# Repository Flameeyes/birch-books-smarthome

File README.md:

<!--
SPDX-FileCopyrightText: 2020 The birch-books-smarthome Authors

SPDX-License-Identifier: MIT
-->

# Birch Books Smart Home

This repository contains code, schematics, documentation and notes to implement a
MCU-controlled LED lights system for the [LEGO Creator Bookshop
set](https://www.lego.com/en-gb/product/bookshop-10270) (10270).

## Further References

Refer to my [blog posts](https://flameeyes.blog/tag/birch-books/) for details.

You can see some pictures of the results on [my Flickr
album](https://www.flickr.com/photos/flameeyes/albums/72157714292772872).

## License

Copyright 2020 The birch-books-smarthome authors.

Permission is hereby granted, free of charge, to any person obtaining a copy of this
software and associated documentation files (the "Software"), to deal in the Software
without restriction, including without limitation the rights to use, copy, modify,
merge, publish, distribute, sublicense, and/or sell copies of the Software, and to
permit persons to whom the Software is furnished to do so, subject to the following
conditions:

The above copyright notice and this permission notice shall be included in all copies or
substantial portions of the Software.

THE SOFTWARE IS PROVIDED "AS IS", WITHOUT WARRANTY OF ANY KIND, EXPRESS OR IMPLIED,
INCLUDING BUT NOT LIMITED TO THE WARRANTIES OF MERCHANTABILITY, FITNESS FOR A PARTICULAR
PURPOSE AND NONINFRINGEMENT. IN NO EVENT SHALL THE AUTHORS OR COPYRIGHT HOLDERS BE
LIABLE FOR ANY CLAIM, DAMAGES OR OTHER LIABILITY, WHETHER IN AN ACTION OF CONTRACT, TORT
OR OTHERWISE, ARISING FROM, OUT OF OR IN CONNECTION WITH THE SOFTWARE OR THE USE OR
OTHER DEALINGS IN THE SOFTWARE.

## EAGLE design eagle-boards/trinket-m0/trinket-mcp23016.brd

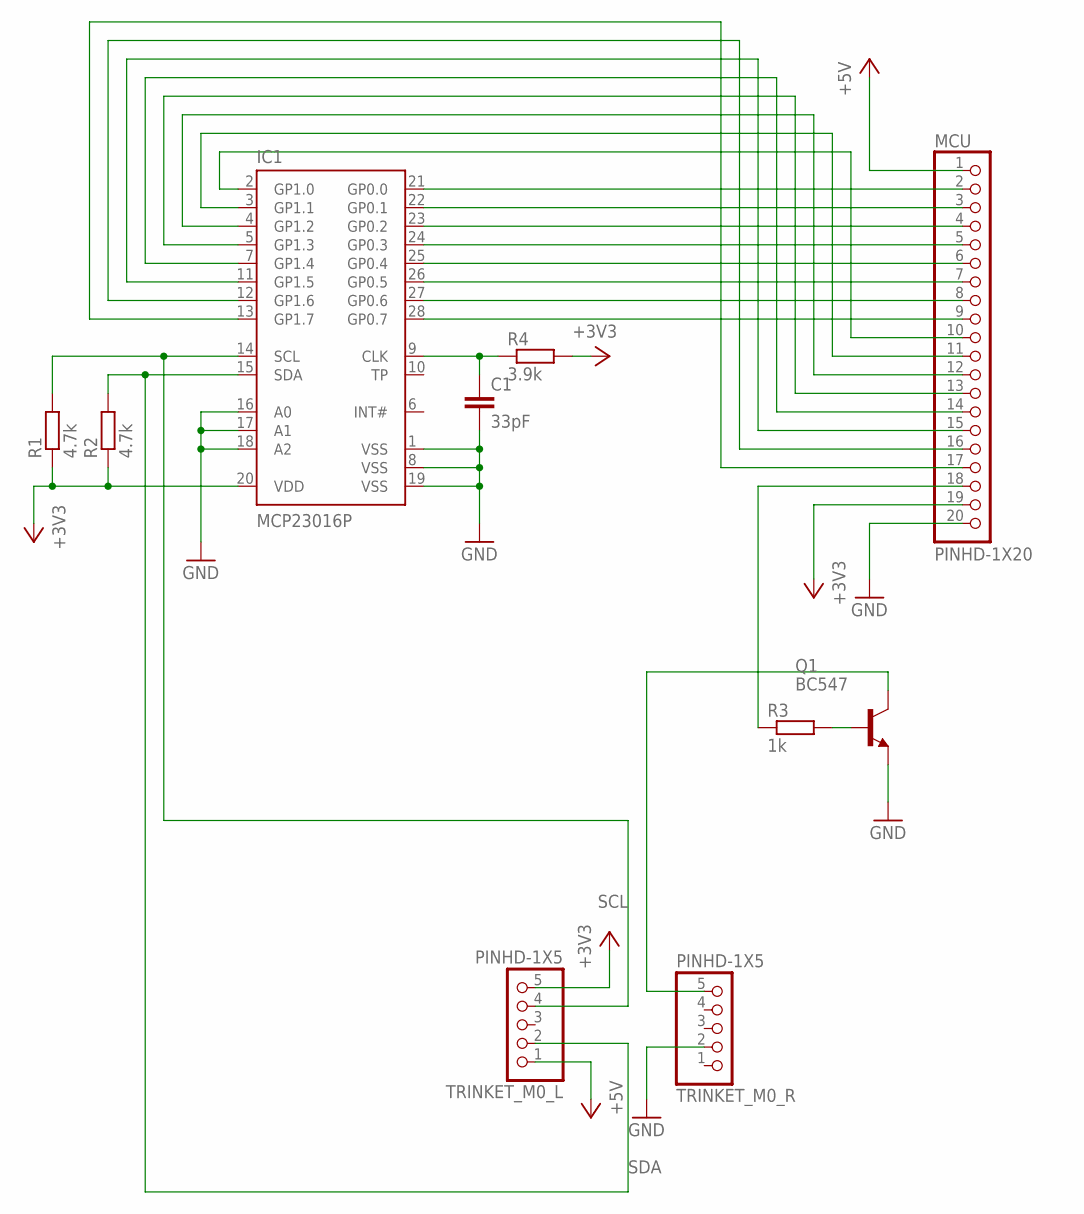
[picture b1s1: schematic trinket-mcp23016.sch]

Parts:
C1: 33pF; C025-025X050
IC1: MCP23016P; DIL28-3
MCU: PINHD-1X20; 1X20
Q1: BC547; TO92
R1, R2: 4.7k; 0207/10
R3: 1k; 0207/10
R4: 3.9k; 0207/10
TRINKET_M0_L, TRINKET_M0_R: PINHD-1X5; 1X05

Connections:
+3V3: IC1.20 (VDD), MCU.19, R1.1, R2.1, R4.2, TRINKET_M0_L.5
+5V: MCU.1, TRINKET_M0_L.1
GND: C1.2, IC1.1 (VSS), IC1.8 (VSS), IC1.16 (A0), IC1.17 (A1), IC1.18 (A2), IC1.19 (VSS), MCU.20, Q1.1 (E), TRINKET_M0_R.2
unnamed: IC1.21 (GP0.0), MCU.2
unnamed: IC1.22 (GP0.1), MCU.3
unnamed: IC1.23 (GP0.2), MCU.4
unnamed: IC1.24 (GP0.3), MCU.5
unnamed: IC1.25 (GP0.4), MCU.6
unnamed: IC1.26 (GP0.5), MCU.7
unnamed: IC1.27 (GP0.6), MCU.8
unnamed: IC1.28 (GP0.7), MCU.9
unnamed: IC1.2 (GP1.0), MCU.10
unnamed: IC1.3 (GP1.1), MCU.11
unnamed: IC1.4 (GP1.2), MCU.12
unnamed: IC1.5 (GP1.3), MCU.13
unnamed: IC1.7 (GP1.4), MCU.14
unnamed: IC1.11 (GP1.5), MCU.15
unnamed: IC1.12 (GP1.6), MCU.16
unnamed: IC1.13 (GP1.7), MCU.17
unnamed: Q1.2 (B), R3.2
unnamed: MCU.18, R3.1
unnamed: Q1.3 (C), TRINKET_M0_R.5
unnamed: C1.1, IC1.9 (CLK), R4.1
SCL: IC1.14 (SCL), R1.2, TRINKET_M0_L.4
SDA: IC1.15 (SDA), R2.2, TRINKET_M0_L.2

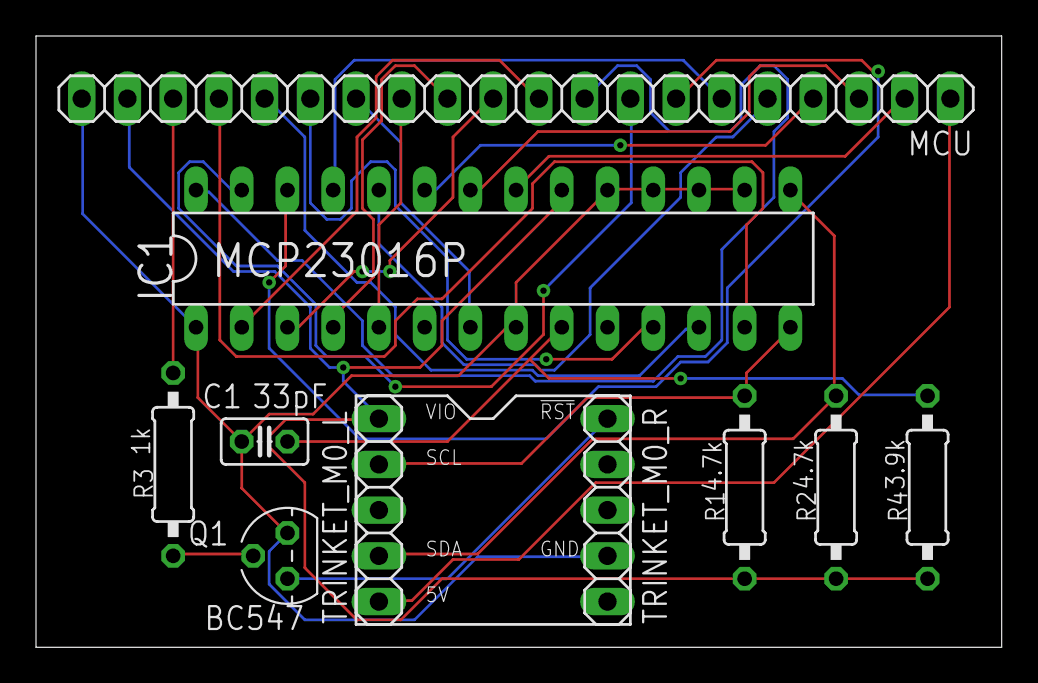
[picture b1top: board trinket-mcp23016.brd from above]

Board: 2 copper layers, 53.6 x 34.0 mm, 10 parts (0 on the bottom side), 25 nets.

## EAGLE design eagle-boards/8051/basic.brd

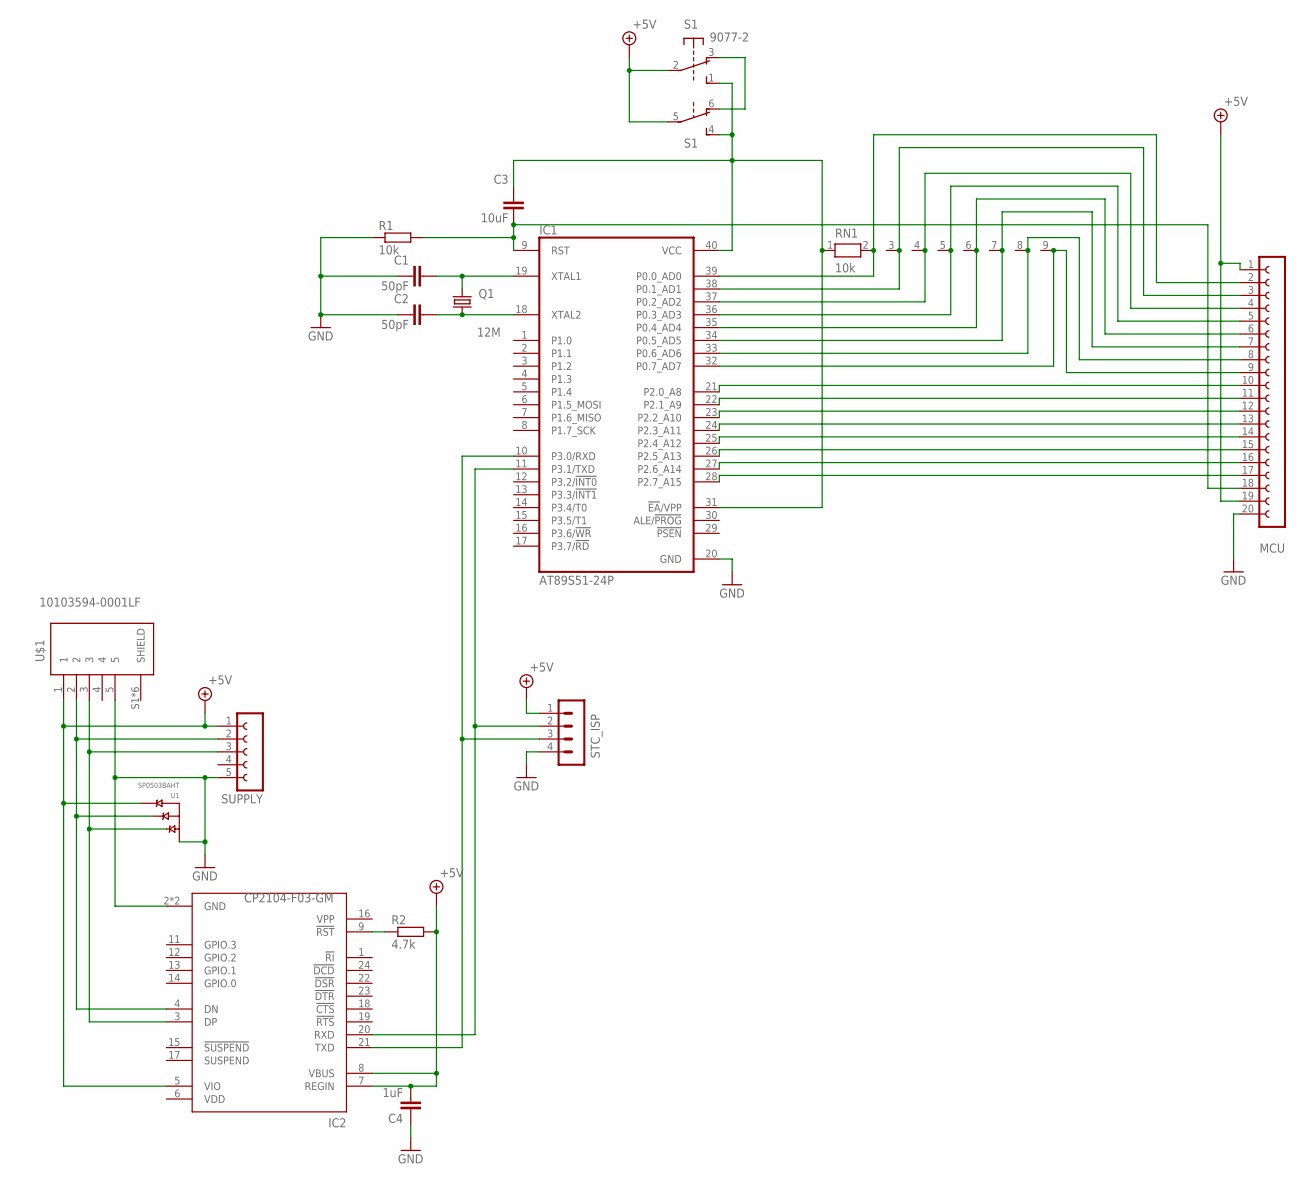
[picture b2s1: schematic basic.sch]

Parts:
C1, C2: 50pF; C050-025X075
C3: 10uF; C025-025X050
C4: 1uF; C025-025X050
IC1: AT89S51-24P; DIL40
IC2: CP2104-F03-GM; QFN50P400X400X80-25N
MCU: FE20-1; FE20
Q1: 12M; HC49U70
R1: 10k; 0207/10
R2: 4.7k; 0207/10
RN1: 10k; RN-9
S1: 9077-2
STC_ISP: MA04-1
SUPPLY: FE05-1
U1: SP0503BAHT; SOT143
U$1: 10103594-0001LF; FCI_10103594-0001LF

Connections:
+5V: C4.2, IC2.5 (VIO), IC2.7 (REGIN), IC2.8 (VBUS), MCU.1, MCU.19, R2.2, S1.2, S1.5, STC_ISP.1, SUPPLY.1, U1.4 (C), U$1.1
GND: C1.1, C2.1, C4.1, IC1.20 (GND), IC2.2 (GND), IC2.25 (GND), MCU.20, R1.1, STC_ISP.4, SUPPLY.5, U1.1 (GND), U$1.5
unnamed: IC2.4 (DN), SUPPLY.2, U1.3 (B), U$1.2
unnamed: IC1.28 (P2.7_A15), MCU.17
unnamed: C1.2, IC1.19 (XTAL1), Q1.2
unnamed: C2.2, IC1.18 (XTAL2), Q1.1
unnamed: C3.2, IC1.9 (RST), MCU.18, R1.2
unnamed: IC1.27 (P2.6_A14), MCU.16
unnamed: IC1.38 (P0.1_AD1), MCU.3, RN1.3
unnamed: IC1.26 (P2.5_A13), MCU.15
unnamed: IC1.25 (P2.4_A12), MCU.14
unnamed: IC1.36 (P0.3_AD3), MCU.5, RN1.5
unnamed: IC1.35 (P0.4_AD4), MCU.6, RN1.6
unnamed: IC1.34 (P0.5_AD5), MCU.7, RN1.7
unnamed: IC1.33 (P0.6_AD6), MCU.8, RN1.8
unnamed: IC1.32 (P0.7_AD7), MCU.9, RN1.9
unnamed: IC1.24 (P2.3_A11), MCU.13
unnamed: IC1.23 (P2.2_A10), MCU.12
unnamed: IC1.22 (P2.1_A9), MCU.11
unnamed: IC1.10 (P3.0/RXD), IC2.21 (TXD), STC_ISP.3
unnamed: IC1.21 (P2.0_A8), MCU.10
unnamed: IC2.3 (DP), SUPPLY.3, U1.2 (A), U$1.3
unnamed: IC1.37 (P0.2_AD2), MCU.4, RN1.4
unnamed: S1.3 (O), S1.6 (O)
unnamed: IC2.9 (!RST!), R2.1
unnamed: IC1.39 (P0.0_AD0), MCU.2, RN1.2
unnamed: C3.1, IC1.31 (!EA!/VPP), IC1.40 (VCC), RN1.1, S1.1 (S), S1.4 (S)
unnamed: IC1.11 (P3.1/TXD), IC2.20 (RXD), STC_ISP.2
VDD: IC2.6 (VDD)

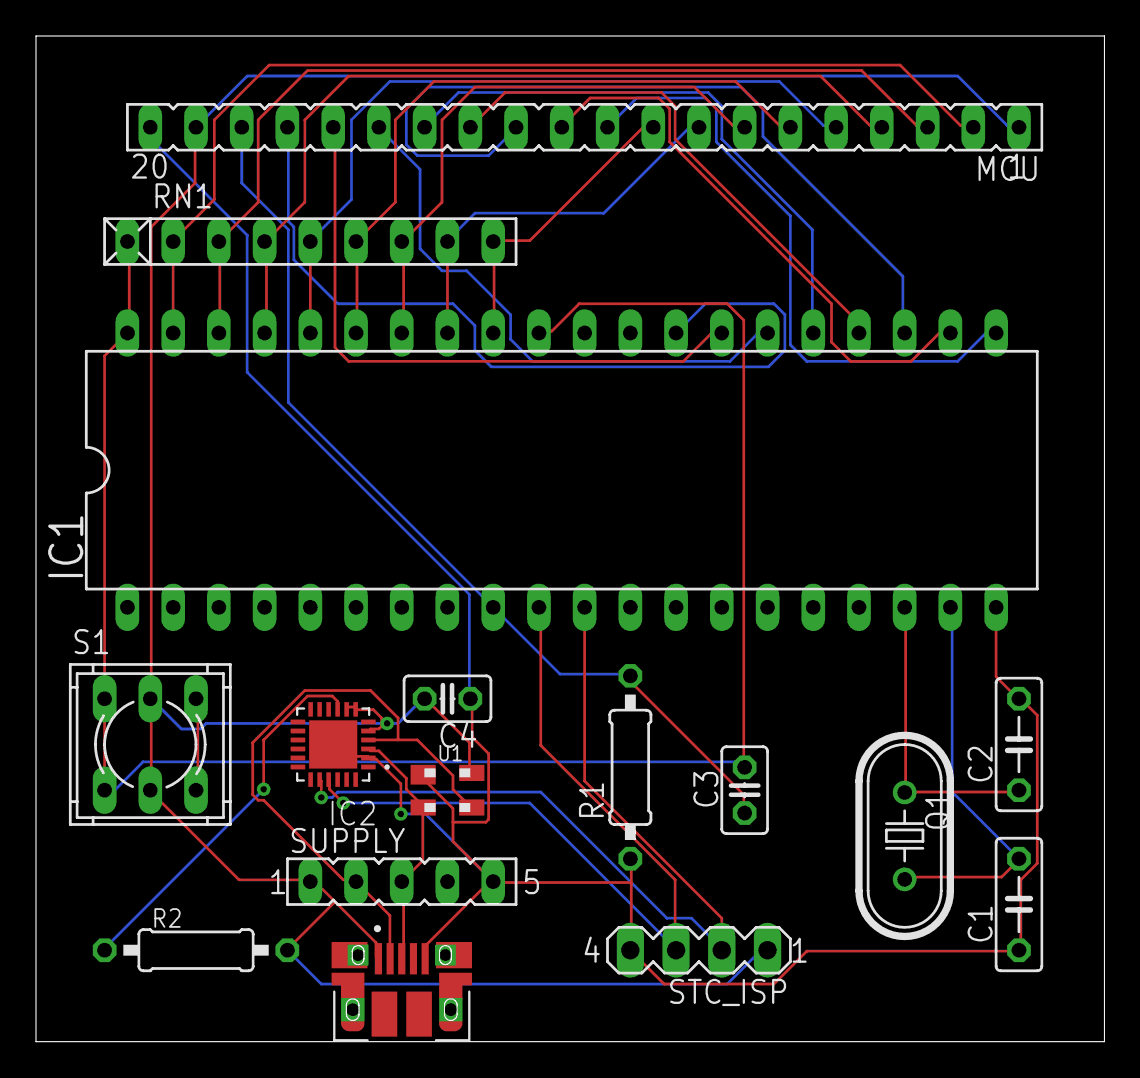
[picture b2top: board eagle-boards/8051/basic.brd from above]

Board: 2 copper layers, 59.4 x 55.9 mm, 16 parts (0 on the bottom side), 28 nets.

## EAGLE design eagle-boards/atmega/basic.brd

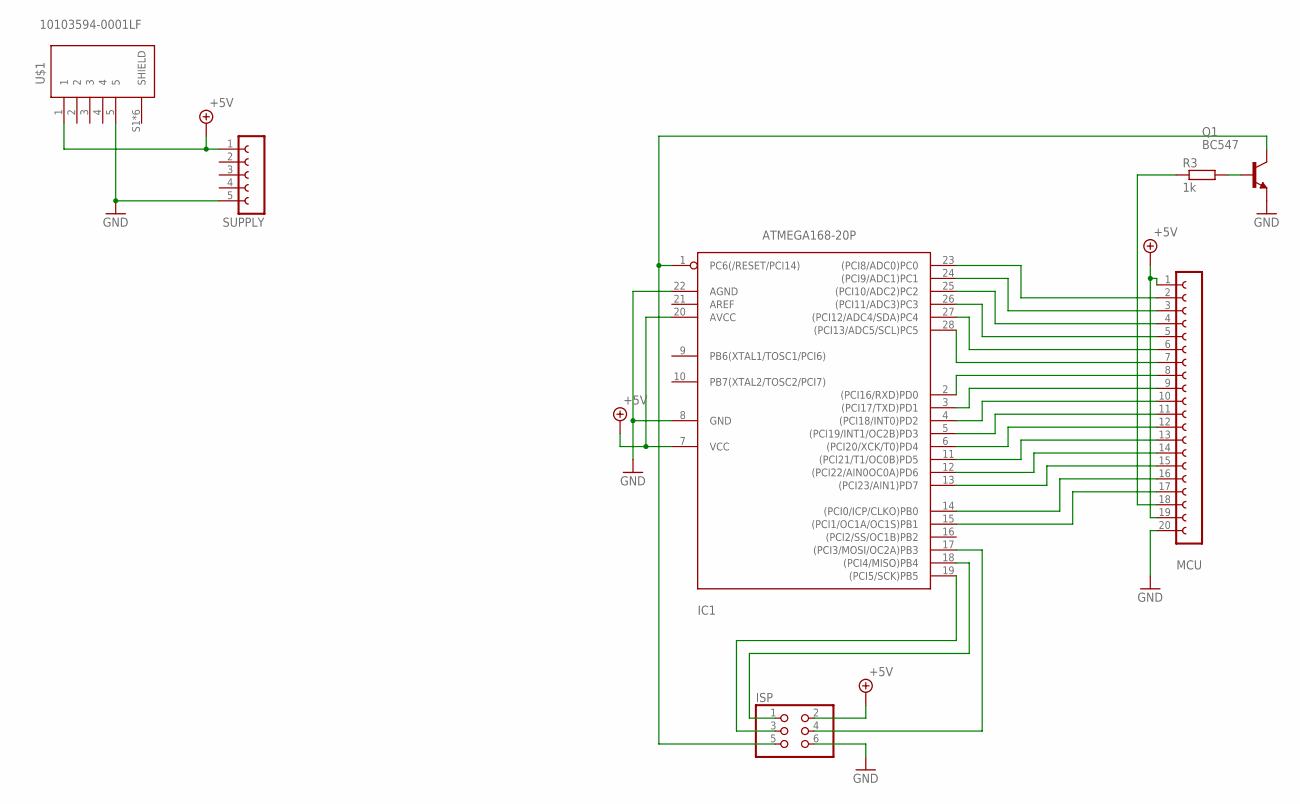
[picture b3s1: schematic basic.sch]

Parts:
IC1: ATMEGA168-20P; DIL28-3
ISP: PINHD-2X3; 2X03
MCU: FE20-1; FE20
Q1: BC547; TO92
R3: 1k; 0207/10
SUPPLY: FE05-1
U$1: 10103594-0001LF; FCI_10103594-0001LF

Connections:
+5V: IC1.7 (VCC), IC1.20 (AVCC), ISP.2, MCU.1, MCU.19, SUPPLY.1, U$1.1
GND: IC1.8 (GND), IC1.22 (AGND), ISP.6, MCU.20, Q1.1 (E), SUPPLY.5, U$1.5
unnamed: IC1.17 ((PCI3/MOSI/OC2A)PB3), ISP.4
unnamed: MCU.18, R3.1
unnamed: IC1.18 ((PCI4/MISO)PB4), ISP.1
unnamed: IC1.19 ((PCI5/SCK)PB5), ISP.3
unnamed: IC1.23 ((PCI8/ADC0)PC0), MCU.2
unnamed: IC1.24 ((PCI9/ADC1)PC1), MCU.3
unnamed: IC1.25 ((PCI10/ADC2)PC2), MCU.4
unnamed: IC1.26 ((PCI11/ADC3)PC3), MCU.5
unnamed: IC1.27 ((PCI12/ADC4/SDA)PC4), MCU.6
unnamed: IC1.28 ((PCI13/ADC5/SCL)PC5), MCU.7
unnamed: IC1.2 ((PCI16/RXD)PD0), MCU.8
unnamed: IC1.3 ((PCI17/TXD)PD1), MCU.9
unnamed: IC1.4 ((PCI18/INT0)PD2), MCU.10
unnamed: IC1.5 ((PCI19/INT1/OC2B)PD3), MCU.11
unnamed: IC1.6 ((PCI20/XCK/T0)PD4), MCU.12
unnamed: IC1.11 ((PCI21/T1/OC0B)PD5), MCU.13
unnamed: Q1.2 (B), R3.2
unnamed: IC1.12 ((PCI22/AIN0OC0A)PD6), MCU.14
unnamed: IC1.1 (PC6(/RESET/PCI14)), ISP.5, Q1.3 (C)
unnamed: IC1.13 ((PCI23/AIN1)PD7), MCU.15
unnamed: IC1.14 ((PCI0/ICP/CLKO)PB0), MCU.16
unnamed: IC1.15 ((PCI1/OC1A/OC1S)PB1), MCU.17

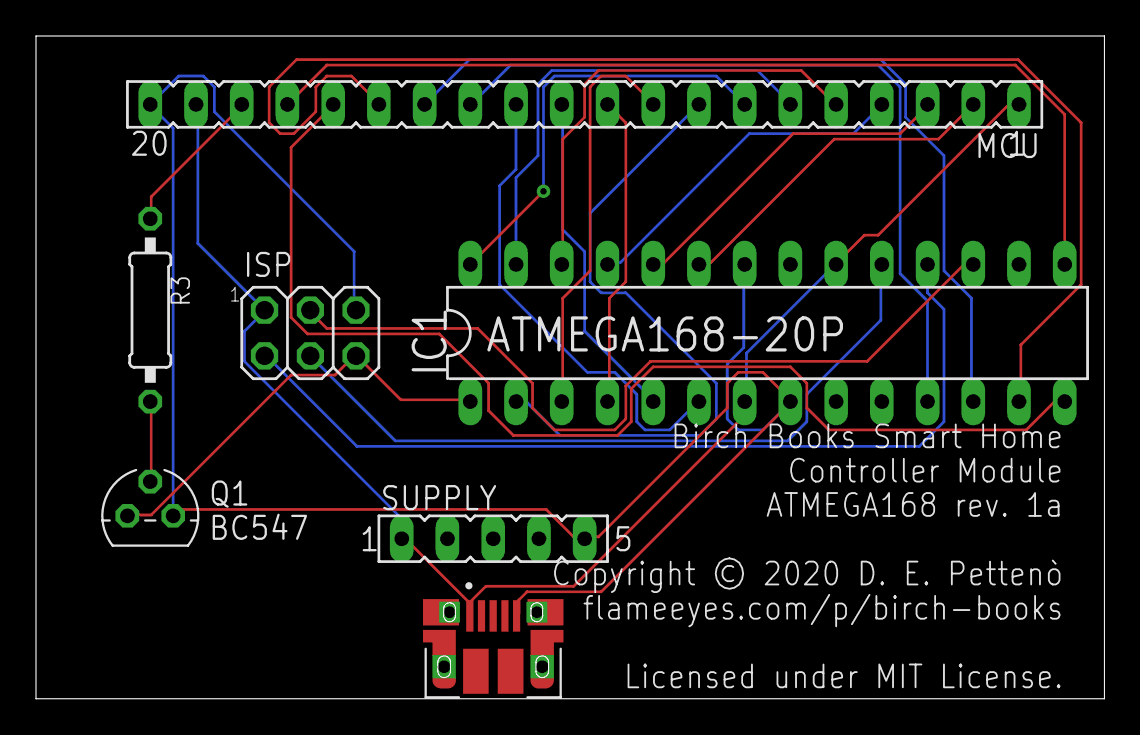
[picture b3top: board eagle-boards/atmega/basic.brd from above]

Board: 2 copper layers, 59.4 x 36.8 mm, 7 parts (0 on the bottom side), 24 nets.

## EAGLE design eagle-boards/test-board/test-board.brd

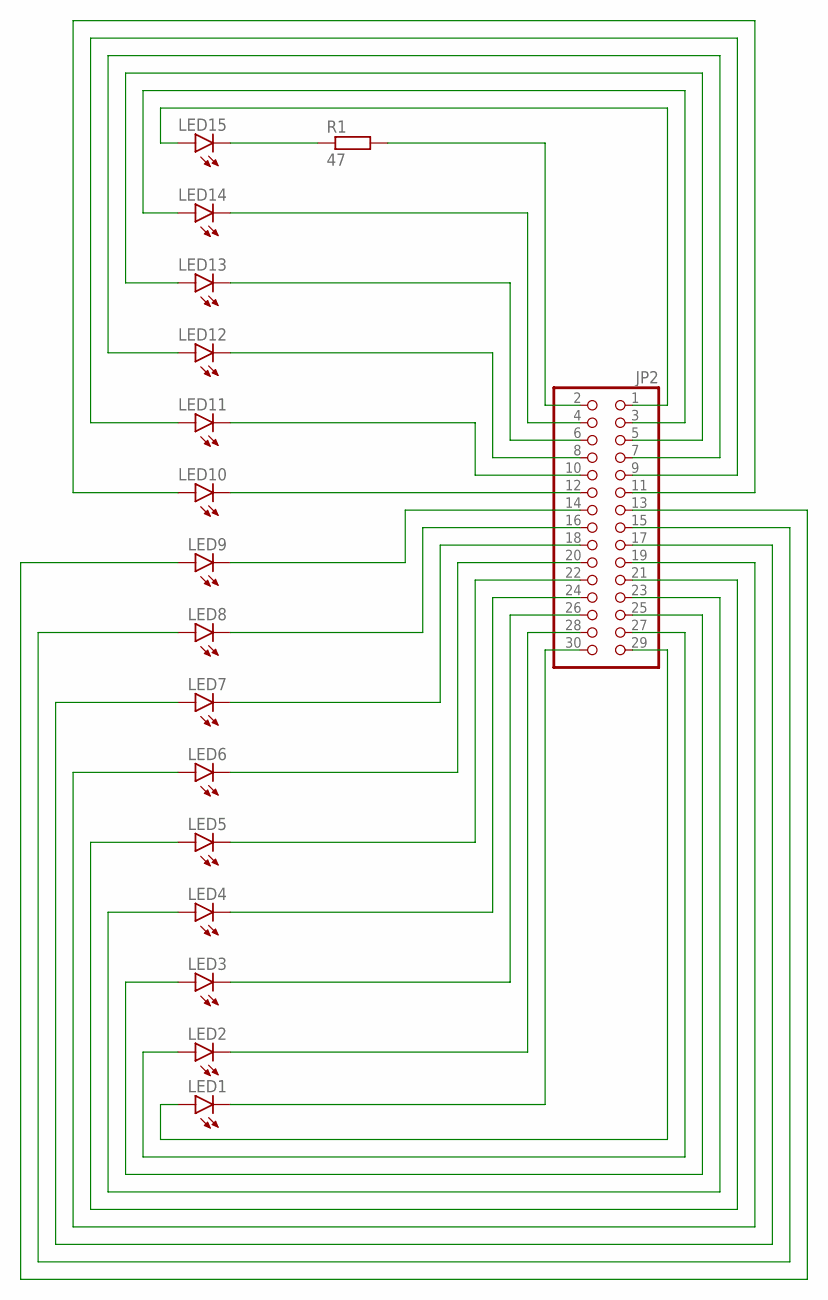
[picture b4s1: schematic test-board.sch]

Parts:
JP2: PINHD-2X15; 2X15
LED1, LED2, LED3, LED4, LED5, LED6, LED7, LED8, LED9, LED10, LED11, LED12, LED13, LED14, LED15: LED5MM
R1: 47; 0207/10

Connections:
unnamed: JP2.2, R1.2
unnamed: JP2.4, LED14.K (C)
unnamed: JP2.6, LED13.K (C)
unnamed: JP2.8, LED12.K (C)
unnamed: JP2.10, LED11.K (C)
unnamed: JP2.12, LED10.K (C)
unnamed: JP2.30, LED1.K (C)
unnamed: JP2.28, LED2.K (C)
unnamed: JP2.26, LED3.K (C)
unnamed: JP2.24, LED4.K (C)
unnamed: JP2.22, LED5.K (C)
unnamed: JP2.20, LED6.K (C)
unnamed: JP2.18, LED7.K (C)
unnamed: JP2.16, LED8.K (C)
unnamed: JP2.14, LED9.K (C)
unnamed: JP2.1, LED15.A
unnamed: JP2.3, LED14.A
unnamed: JP2.5, LED13.A
unnamed: JP2.7, LED12.A
unnamed: JP2.9, LED11.A
unnamed: JP2.11, LED10.A
unnamed: JP2.29, LED1.A
unnamed: JP2.27, LED2.A
unnamed: JP2.25, LED3.A
unnamed: JP2.23, LED4.A
unnamed: JP2.21, LED5.A
unnamed: JP2.19, LED6.A
unnamed: JP2.17, LED7.A
unnamed: JP2.15, LED8.A
unnamed: JP2.13, LED9.A
unnamed: LED15.K (C), R1.1

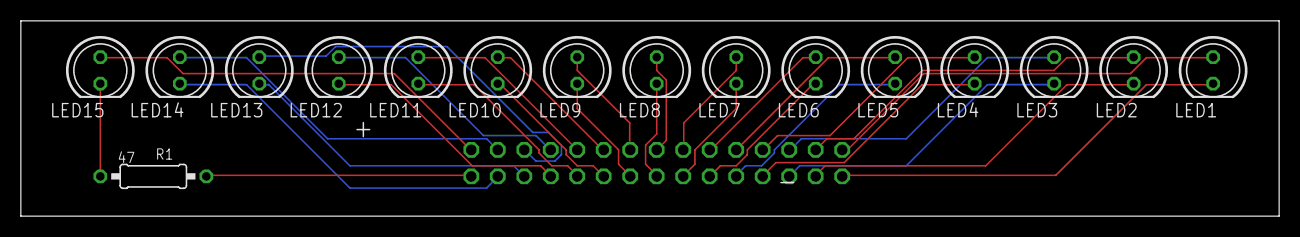
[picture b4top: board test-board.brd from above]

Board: 2 copper layers, 120.6 x 18.7 mm, 17 parts (1 on the bottom side), 31 nets.

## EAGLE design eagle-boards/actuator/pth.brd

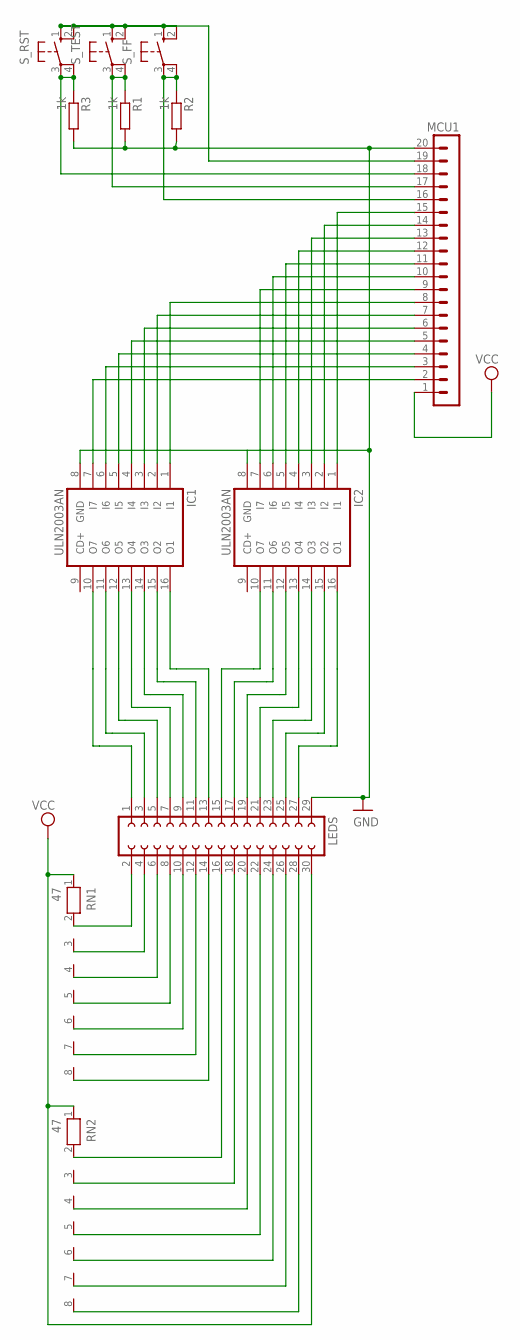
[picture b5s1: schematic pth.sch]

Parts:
IC1, IC2: ULN2003AN; DIL16
LEDS: FE15-2
MCU1: MA20-1
R1, R2, R3: 1k; 0207/10
RN1, RN2: 47; RN-8
S_FF: 10-XX; B3F-10XX
S_RST: 10-XX; B3F-10XX
S_TEST: 10-XX; B3F-10XX

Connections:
GND: IC1.8 (GND), IC2.8 (GND), LEDS.29, MCU1.20, R1.2, R2.2, R3.2
unnamed: IC1.1 (I1), MCU1.8
unnamed: MCU1.19, S_FF.1 (S), S_FF.2 (S1), S_RST.1 (S), S_RST.2 (S1), S_TEST.1 (S), S_TEST.2 (S1)
unnamed: IC1.7 (I7), MCU1.2
unnamed: IC1.6 (I6), MCU1.3
unnamed: IC1.5 (I5), MCU1.4
unnamed: IC1.4 (I4), MCU1.5
unnamed: IC1.3 (I3), MCU1.6
unnamed: IC1.2 (I2), MCU1.7
unnamed: IC2.7 (I7), MCU1.9
unnamed: IC2.6 (I6), MCU1.10
unnamed: IC2.5 (I5), MCU1.11
unnamed: IC2.4 (I4), MCU1.12
unnamed: IC2.3 (I3), MCU1.13
unnamed: IC2.2 (I2), MCU1.14
unnamed: IC2.1 (I1), MCU1.15
unnamed: LEDS.2, RN1.2
unnamed: MCU1.18, R3.1, S_RST.3, S_RST.4 (P1)
unnamed: MCU1.17, R1.1, S_TEST.3, S_TEST.4 (P1)
unnamed: MCU1.16, R2.1, S_FF.3, S_FF.4 (P1)
unnamed: IC2.16 (O1), LEDS.27
unnamed: IC2.15 (O2), LEDS.25
unnamed: IC2.14 (O3), LEDS.23
unnamed: IC2.13 (O4), LEDS.21
unnamed: IC2.12 (O5), LEDS.19
unnamed: IC2.11 (O6), LEDS.17
unnamed: IC2.10 (O7), LEDS.15
unnamed: IC1.16 (O1), LEDS.13
unnamed: IC1.15 (O2), LEDS.11
unnamed: IC1.14 (O3), LEDS.9
unnamed: IC1.13 (O4), LEDS.7
unnamed: IC1.12 (O5), LEDS.5
unnamed: IC1.11 (O6), LEDS.3
unnamed: IC1.10 (O7), LEDS.1
unnamed: LEDS.4, RN1.3
unnamed: LEDS.6, RN1.4
unnamed: LEDS.8, RN1.5
unnamed: LEDS.10, RN1.6
unnamed: LEDS.12, RN1.7
unnamed: LEDS.14, RN1.8
unnamed: LEDS.16, RN2.2
unnamed: LEDS.18, RN2.3
unnamed: LEDS.20, RN2.4
unnamed: LEDS.22, RN2.5
unnamed: LEDS.24, RN2.6
unnamed: LEDS.26, RN2.7
unnamed: LEDS.28, RN2.8
VCC: LEDS.30, MCU1.1, RN1.1, RN2.1

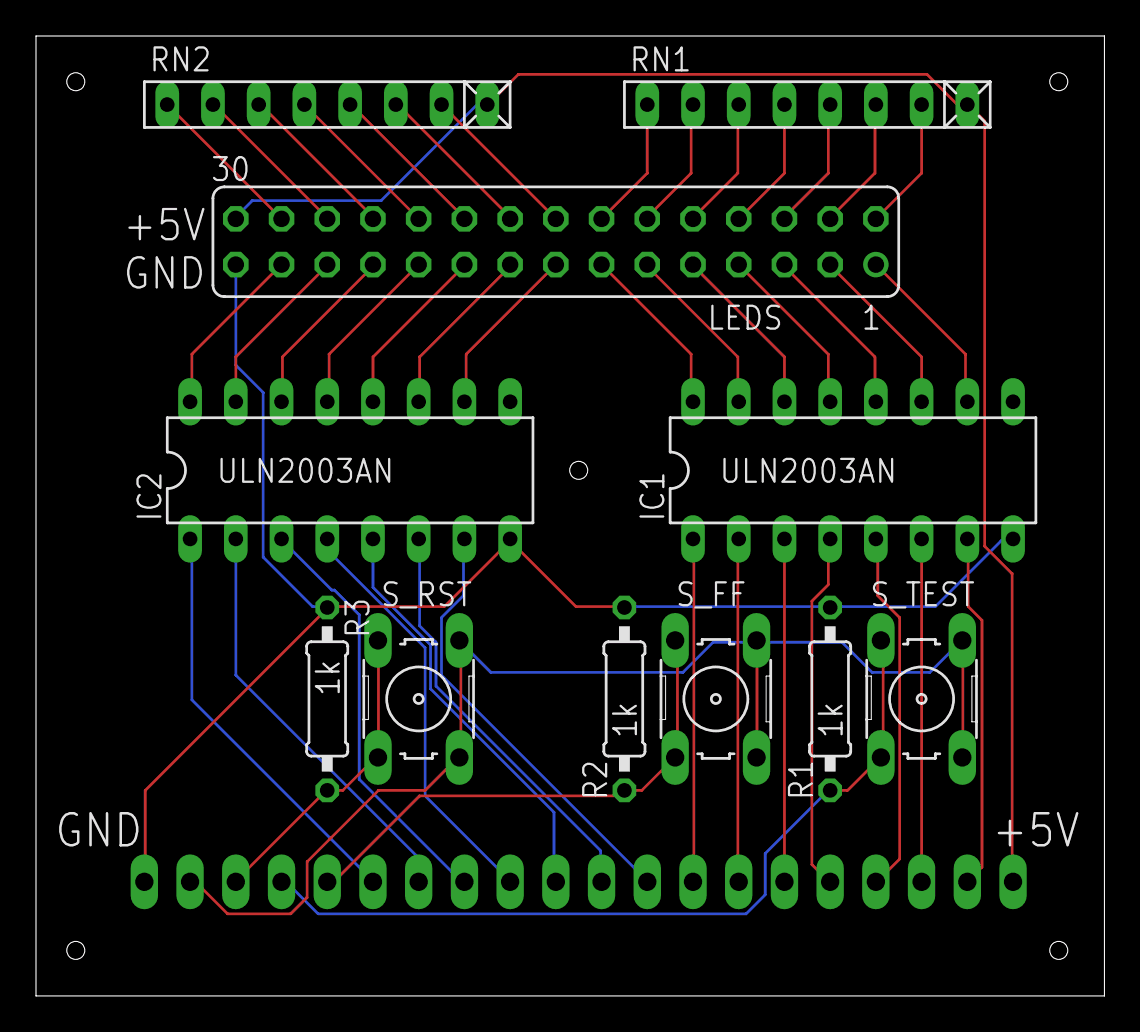
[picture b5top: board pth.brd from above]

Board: 2 copper layers, 59.4 x 53.3 mm, 12 parts (1 on the bottom side), 48 nets.

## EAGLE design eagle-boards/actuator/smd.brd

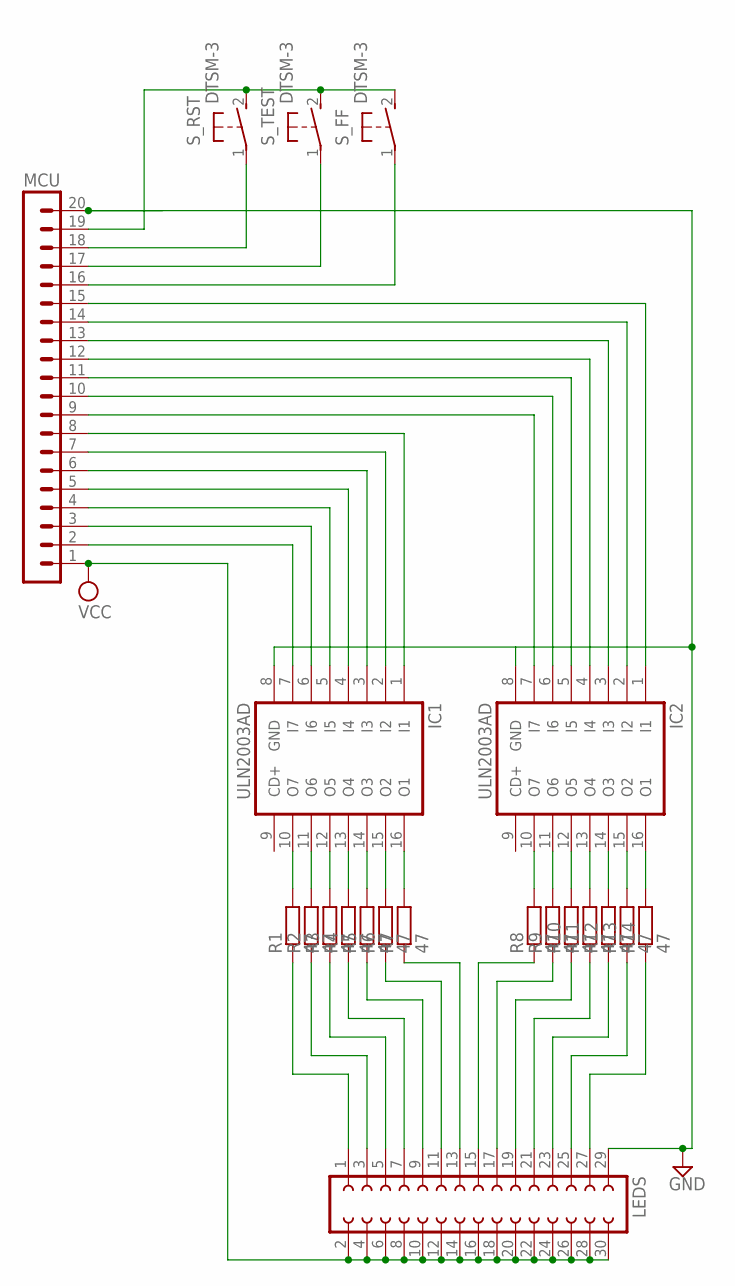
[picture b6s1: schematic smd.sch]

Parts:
IC1, IC2: ULN2003AD; SO16
LEDS: FE15-2
MCU: MA20-1
R1, R2, R3, R4, R5, R6, R7, R8, R9, R10, R11, R12, R13, R14: 47; M0805
S_FF: DTSM-3
S_RST: DTSM-3
S_TEST: DTSM-3

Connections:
GND: IC1.8 (GND), IC2.8 (GND), LEDS.29, MCU.20
unnamed: IC1.1 (I1), MCU.8
unnamed: MCU.19, S_FF.2, S_RST.2, S_TEST.2
unnamed: IC1.7 (I7), MCU.2
unnamed: IC1.6 (I6), MCU.3
unnamed: IC1.5 (I5), MCU.4
unnamed: IC1.4 (I4), MCU.5
unnamed: IC1.3 (I3), MCU.6
unnamed: IC1.2 (I2), MCU.7
unnamed: IC2.7 (I7), MCU.9
unnamed: IC2.6 (I6), MCU.10
unnamed: IC2.5 (I5), MCU.11
unnamed: IC2.4 (I4), MCU.12
unnamed: IC2.3 (I3), MCU.13
unnamed: IC2.2 (I2), MCU.14
unnamed: IC2.1 (I1), MCU.15
unnamed: MCU.18, S_RST.1
unnamed: MCU.17, S_TEST.1
unnamed: MCU.16, S_FF.1
unnamed: IC1.10 (O7), R1.2
unnamed: IC1.11 (O6), R2.2
unnamed: IC1.12 (O5), R3.2
unnamed: IC1.13 (O4), R4.2
unnamed: IC1.14 (O3), R5.2
unnamed: IC1.15 (O2), R6.2
unnamed: IC1.16 (O1), R7.2
unnamed: IC2.10 (O7), R8.2
unnamed: IC2.11 (O6), R9.2
unnamed: IC2.12 (O5), R10.2
unnamed: IC2.13 (O4), R11.2
unnamed: IC2.14 (O3), R12.2
unnamed: IC2.15 (O2), R13.2
unnamed: IC2.16 (O1), R14.2
unnamed: LEDS.27, R14.1
unnamed: LEDS.25, R13.1
unnamed: LEDS.23, R12.1
unnamed: LEDS.21, R11.1
unnamed: LEDS.19, R10.1
unnamed: LEDS.17, R9.1
unnamed: LEDS.15, R8.1
unnamed: LEDS.13, R7.1
unnamed: LEDS.11, R6.1
unnamed: LEDS.9, R5.1
unnamed: LEDS.7, R4.1
unnamed: LEDS.5, R3.1
unnamed: LEDS.3, R2.1
unnamed: LEDS.1, R1.1
VCC: LEDS.2, LEDS.4, LEDS.6, LEDS.8, LEDS.10, LEDS.12, LEDS.14, LEDS.16, LEDS.18, LEDS.20, LEDS.22, LEDS.24, LEDS.26, LEDS.28, LEDS.30, MCU.1

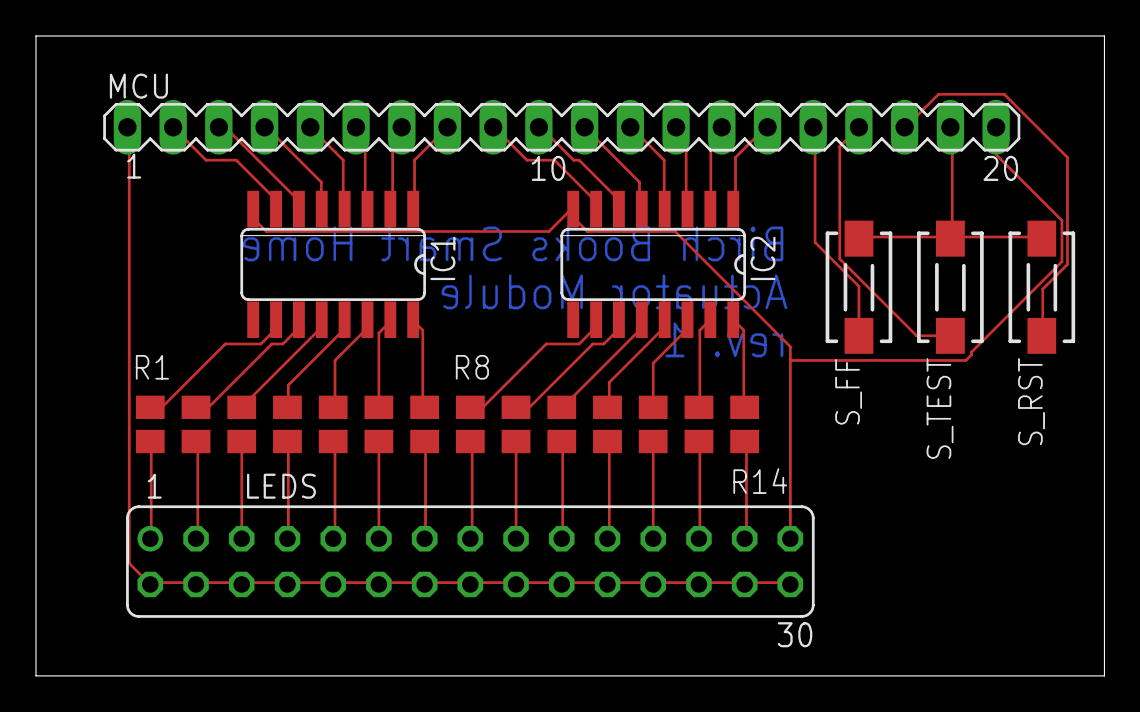
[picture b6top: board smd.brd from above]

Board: 2 copper layers, 59.4 x 35.5 mm, 21 parts (0 on the bottom side), 48 nets.

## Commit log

2020-04-04 Initial import.
2020-04-04 Add the very base of the firmware implementation.
    This is effectively a modified demo counter.
2020-04-04 Import the first basic version of the PCB
    This includes the AutoDesk Eagle files describing a board that includes the two darlington arrays, the connector for the LEDs, control buttons and ISP headers for both the Microchip and STC variants 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
2020-04-06 Use the AT89x52 header instead of defining registers manually.
    While the STC89C52 I'm using is not 100% identical in registers, all the
    features I want are present in this header, and that way it will work on both.
2020-04-06 Split the actuation into its own board.
    Note that the previous design was broken, as the Darlingtons weren't being grounded, but rather joined to Vcc.
2020-04-09 Fix significant mistakes in the controller board.
    The capacitors to stabilise the crystal need to be a bit beefier, make space for them.
    Replace the pin header with a female header for the connection to the actuator board.
    Necessary: add a resistor network between P0 and the connector.
    P0 is the only port needing pull-up resistors.
2020-04-09 Move boards on a separate directory.
    This allows arranging them by implementation.
    The actuator module is reusable, the 8051 board isn't.
2020-04-09 Rename actuator-module.
    This allows creating alternative versions of the module. This design is fully SMD, ready for turnkey production.
    But a through-hole solder-at-home allows faster prototyping.
2020-04-09 Add through-hole variant of the actuator board.
    This should make prototyping faster/easier.
2020-04-09 Wire the inputs to logic.
    - While FF is pressed, timer goes 1000x (not final.)
    - If FF is pressed at startup, put a chase light pattern into the ports,
    for testing.
    - If TEST is pressed toggle between all-on and not.
    Note that sdcc is buggy and does not handle logic correctly, or
    functions. Or constants. So use a lot of #define instead and consider this
2020-04-09 One more chase pattern, to make this easier to test.
2020-04-10 Actually write the firmware for the 8051 control board.
    This includes all the expected logic to control the board, and a lot of
    documentation of what's going on.
    Note that this targets in particular the 8051 clones that include Timer 2,
    since it's the easier auto-reload 16-bit implementation, and it includes
    some explicit workarounds for sdcc code generation.
2020-04-10 Micro-optimization: sdcc doesn't optimise these two operations the same way.
2020-04-10 Micro-optimisation, set P1 bit registers instead.
2020-04-10 Micro-optimisation, use P2 bit register to test inputs.
2020-04-10 Micro-optimisation, force sdcc to collapse branches.
2020-04-10 Downgrade ticktime to 16-bit.
    Add a definition of MAXTICK, and a description of why that's important. This improves the generated code quite a bit.
2020-04-10 Rollover the clock at MAXTICK.
2020-04-10 Reduce the schedule from 20 "hours" to 16.
    This simplifies a lot of the math below, while keeping the one real hour full cycle.
2020-04-10 Simplify code by using "round" numbers.
    This changes the seconds / virtual_hour value to 256 (up from 225), making
    most of the math in this code straightforward binary operations.
    Note that sdcc is unable to understand that "x / 256" is the same as "x >> 8".
2020-04-10 Micro-optimisation: sdcc does not understand this value is only 4-bit wide.
2020-04-10 Use ticks within the code instead of seconds.
    Except for where we need it to represent a second, we can more easily
    calculate things directly in ticks.
2020-04-10 Micro-optimisation: size the bit variable to 8-bit.
2020-04-10 Micro-optimisation: avoid jump in self-test mode.
2020-04-10 Simplify the output port.
2020-04-15 Improve documentation of the boards.
2020-04-19 Follow REUSE (https://reuse.software/) specifications of licensing.
2020-04-23 Move the debouncing of TEST at the top.
2020-04-23 Run clang-format.
2020-04-23 Move the 8051 build out of the fw/ directory.
    I moved the boards onto a different structure anyway.
2020-04-23 Update .gitignore too.
2020-04-23 Invert house bedroom lamp and light lines.
2020-04-23 Increase the "fast forward" speed to 64x.
    This allows the schedule to complete in one minute, which is the limit for
    most GIFs.
2020-05-16 Add pre-commit GitHub Action.
2020-05-16 Add reuse to the pre-commit hooks.
2020-05-16 Fix up trailing whitespace.
2020-06-13 Update pre-commit configuration to run on main branch.
2020-07-18 Introduce Adafruit Trinket M0-based controller boards.
    The two boards are pretty much identical except for the GPIO expander used:
    - MCP23016 is an old, deprecated chip, but still found on the market, it needs two more passives to work and doesn't offer pull-up or pull-downs for inputs. It requires a non-main branch version of t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
    - MCP23017 is more recent and recommended; it's supported out of the box by the MCP230xx library. For it to be supported with the same CircuitPython code, the board puts it on non-default address 33.
2020-07-18 Untested version of an ATmega48-based controller board.
    This is untested, but should allow using an ATmega48 in a similar way to how the STC89 is used.
2020-07-18 New revision for the STC89C52 controller board.
    Include (optional) CP2104 USB-to-UART adapter to make it easier to program the board in-system.
    Include a latching pushbutton for power, which is also needed to work correctly for in-system programming.
2020-07-18 New revision for the actuator board.
    Fix orientation of buttons to be the same between all three, and include pull-down resistors if the input lines are not pulled down.
2020-07-18 Add a test board for the actuator board.
    This allows testing the actuator without wiring the whole LEGO set harness up.
2020-07-18 Fix whitespace for pre-commit.
2020-07-18 Add SPDX license attachments for the Eagle Boards.
2020-07-18 Ignore VSCode and venv directories.
    The venv directory allows installing pre-commit and similar tools.
2020-07-18 Add CircuitPython-based implementation.
    This requires a modified adafruit_mcp230xx library that supports the MCP23016, but it will work with both the '16 and '17 boards (on different I2C addresses.)
    Note: this version will not work on Trinket M0, and is committed as is to keep track of historical changes!
2020-07-18 CircuitPython Controller: fix to work on Trinket M0.
    Trinket M0 does not support `time.time()`, but does support
    `time.monotonic()`, which is also in seconds and works fine for the need of
    the program. But on the other hand, `monotonic()` returns a floating point
    value.
    Also correct the detection of the MCP23017, and raise an exception if no
    expander is found at all.
2020-07-18 Set up isort for CircuitPython code.
    The special CircuitPython configuration of isort is meant to separate the
    Python standard library modules from CP (or Blinka) modules in the
    sections, for ease of reading.
2020-07-18 Add black and isort to the pre-commit configuration.
2020-07-21 Add a new revision for the actuator board.
    Rotate the board so that the writing is in the same orientation as the controller board once mounted.
    Include +5/GND markings on both connectors.
    Put the MCU connector on the _bottom_ layer, rather than the top.
2020-07-21 Update the test board.
    The new revision is smaller, and reports the connector on the bottom side as expected.
2020-07-24 Re-layout board to align with actuator.
    Also update the microUSB connector to a SnapEDA symbol for an Amphenol connector that appears to be easier to source and solder.
2020-07-24 Update components and layout for 8051 board.
    Replace the microUSB connector to be the same Amphenol part as used in the ATmega board.
    Replace the single electrolytic with a ceramic capacitor, and match the footprint between that and the CP2104 one.
2020-07-26 Replace the wima capacitor object with a generic one.
    This is pretty much the same footprint (except the solder pad is slightly thinner), but it requires one less library, since the xtal's capacitors are coming from rcl as well.
2020-07-26 Clean up the Trinket M0 based boards.
    This makes the two board use the same size, and the same positioning of the common components.
    It also reorients the silkscreen markings on the back to have the same orientation as the actuator board.
    Also mark the used lines from the Trinket, as you can technically use any other MCU that can drive I²C.
2020-07-26 Exclude Eagle files from pre-commit checks.
    It's pointless to clean those up as Eagle will always try modifying them anyway.
2020-07-26 Add check-toml.
2020-07-26 Expand documentation.
    Includes some commentary around the boards, and a link to one of the pictures to explain what this is all about.
2020-07-26 Fix Markdown image syntax.
2020-07-26 Remove trailing whitespace.
2020-07-26 Make the text fit into the silkscreen.
2020-07-26 Align the resistor label.
2020-07-26 Update the capacitor to match the 8051 board.
2020-08-16 Add an ATmega48 based firmware.
    This is based on the board designs in eagle-boards/atmega/ and the original
    8051 firmware.
    Unlike the STC89C52, the ATmega48 MCU has non-linear mapping of the I/Os,
    which makes the room definition a bit more complicated, but otherwise the
    logic of the code is essentially the same.
    Note that the "strobe" test has been removed from this version, because
2020-08-16 Update documentation of ATmega48 board, now that it was tested.
2020-08-16 Remove the "strobe mode" test, as done on the atmega48 firmware.
    The strobe mode is unsafe, as it routes multiple LEDs for the same room
    into the same collector of the Darlington arrays.
2020-08-16 Add clang-format to pre-commit validation.
2020-08-16 Fix pre-commit configuration to ignore trailing whitespace on Eagle boards.
2020-08-16 Backport the ATmega48 changes to the CircuitPython version.
    This includes removing the knuckle pattern (unsafe), and introducing the 1
    second power-on self-test.
2020-09-07 Update pre-commit plugins version.
2020-12-12 Update pre-commit configuration.
2022-05-19 pre-commit: update

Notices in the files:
eagle-boards/8051/basic.brd:
Copyright © 2020 Diego Elio Pettenò
Licensed under MIT License.
eagle-boards/actuator/pth.brd:
Copyright © 2020 D. E. Pettenò
parts and their libraries:
con-molex-usb: (C) 2014 Tomasz Boleslaw CEDRO, cederom@tlen.pl, http://www.tomek.cedro.info.
